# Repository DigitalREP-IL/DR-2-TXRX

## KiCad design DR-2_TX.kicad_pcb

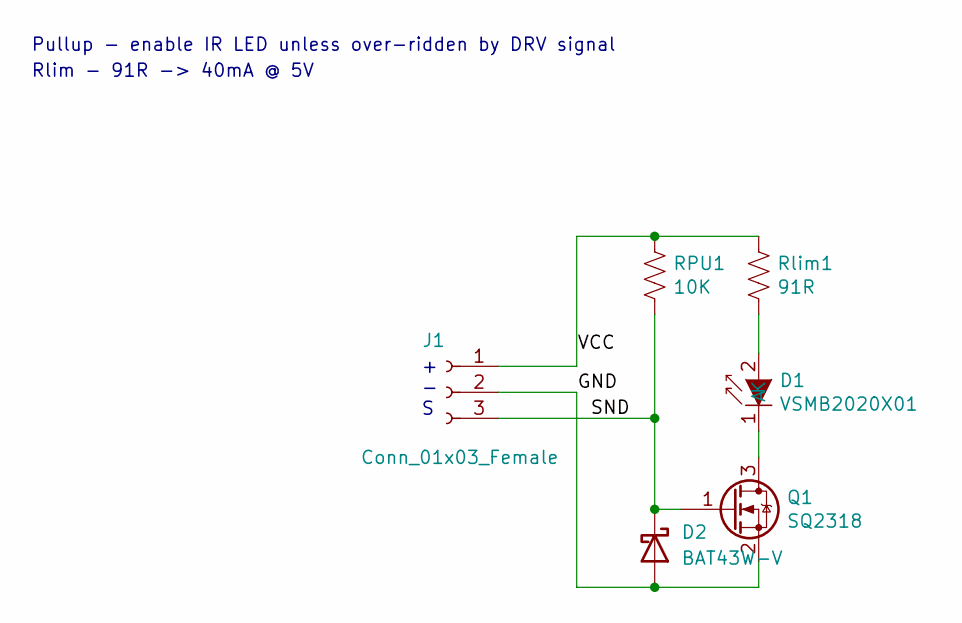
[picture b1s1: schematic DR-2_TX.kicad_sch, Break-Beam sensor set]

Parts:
D1: VSMB2020X01; VSMG28011G
D2: BAT43W-V; D_SOD-123
J1: Conn_01x03_Female; Pin_Header_Angled_1x03_Pitch2.54mm
Q1: SQ2318; SOT-23
RPU1: 10K; R_0603_HandSoldering
Rlim1: 91R; R_0603_HandSoldering

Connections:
/GND: D2.2 (A), J1.2, Q1.2 (S)
/SND: D2.1 (K), J1.3, Q1.1 (G), RPU1.2
/VCC: J1.1, RPU1.1, Rlim1.1
unnamed: D1.1 (K), Q1.3 (D)
unnamed: D1.2 (A), Rlim1.2

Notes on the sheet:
Rlim - 91R -> 40mA @ 5V
Pullup - enable IR LED unless over-ridden by DRV signal
+ - S

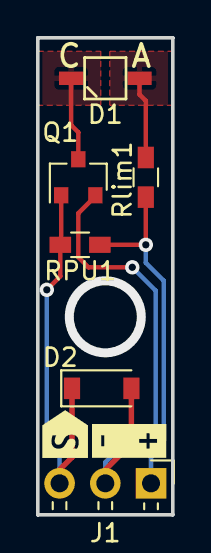
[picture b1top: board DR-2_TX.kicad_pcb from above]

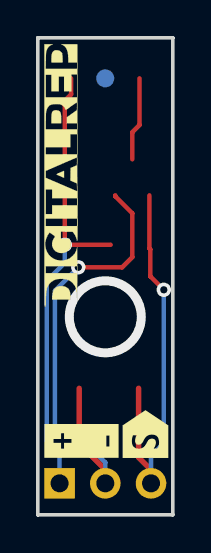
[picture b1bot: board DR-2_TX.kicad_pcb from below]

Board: 2 copper layers, 7.5 x 26.5 mm, 10 parts (2 on the bottom side), 5 nets.

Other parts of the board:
kibuzzard-6377ADC5: G***; kibuzzard-6377ADC5
kibuzzard-6377ADF0: G***; kibuzzard-6377ADF0
kibuzzard-6377B0BC: G***; kibuzzard-6377B0BC
kibuzzard-6377B096: G***; kibuzzard-6377B096

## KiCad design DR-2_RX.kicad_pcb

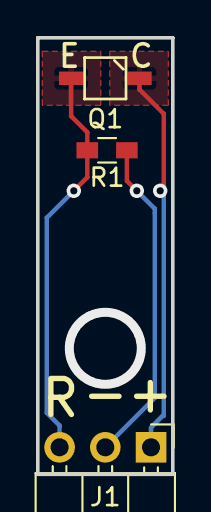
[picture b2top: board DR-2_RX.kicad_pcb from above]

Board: 2 copper layers, 7.5 x 24.2 mm, 3 parts (0 on the bottom side), 3 nets.

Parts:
J1: Conn_01x03_Female; Pin_Header_Angled_1x03_Pitch2.54mm
Q1: Q_Photo_NPN; VSMG28011G
R1: 10K; R_0603_HandSoldering

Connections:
/GND: J1.2, R1.2
/SIG: J1.3, Q1.2, R1.1
/VCC: J1.1, Q1.1

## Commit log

2024-03-14 Initial Commit
    for Github push
2024-03-14 update ignore file
